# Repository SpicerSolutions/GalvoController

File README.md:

# GalvoController
Output ILDA signals using an Arduino or similar

Disclosure.

This schematic is from the following instructable

https://www.instructables.com/id/Arduino-Laser-Show-With-Real-Galvos/

And the board layout is inspired by LevTronics design of the above.

https://www.instructables.com/member/LevTronic/

I'm not an electronics engineer so I take no responsibilty for any issues with the board or design. If you have any advice or helpful amendments please let me know or submit a Pull Request.

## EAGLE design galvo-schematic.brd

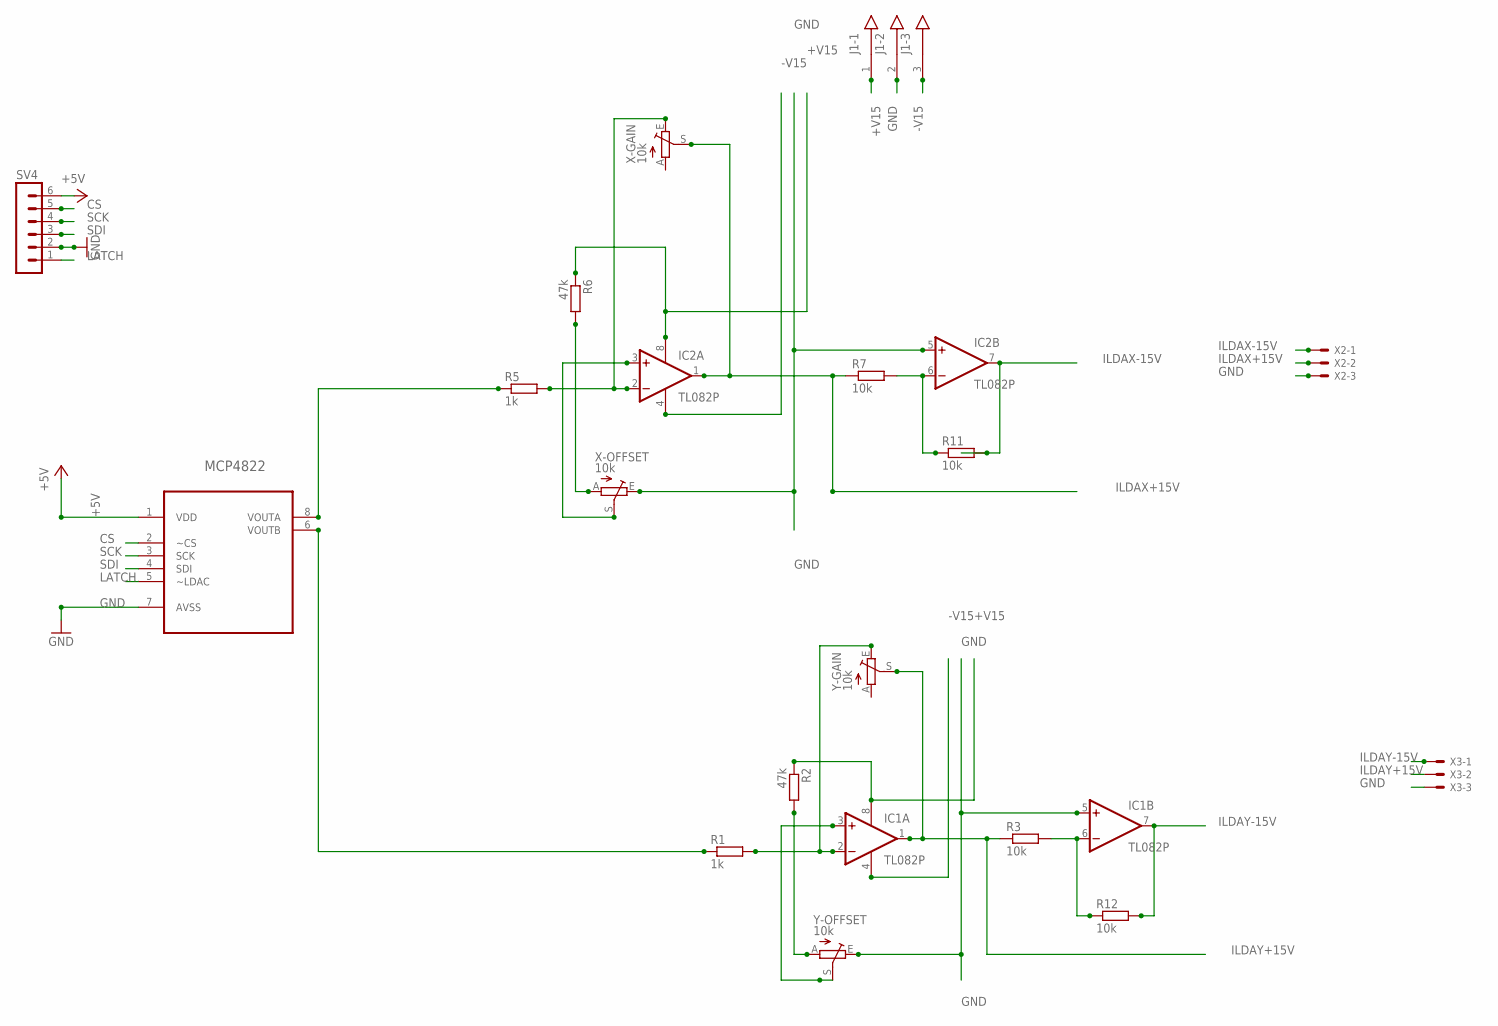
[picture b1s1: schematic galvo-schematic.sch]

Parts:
IC1, IC2: TL082P; DIL08
J1: 0022272031; KK6410-2031_3-PIN
MCP4822: MCP4822-E/P; DIP254P762X432-8
R1, R5: 1k; 0207/10
R2, R6: 47k; 0207/10
R3, R7, R11, R12: 10k; 0207/10
SV4: MA06-1
X2, X3: JST-XH-03-PIN-ROUND-PAD; JST-XH-03-PACKAGE-ROUND-PAD
X-GAIN: 10k; B25P
X-OFFSET: 10k; B25P
Y-GAIN: 10k; B25P
Y-OFFSET: 10k; B25P

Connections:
+5V: MCP4822.1 (VDD), SV4.6
+V15: IC1.8 (V+), IC2.8 (V+), J1.1, R2.1, R6.1
-V15: IC1.4 (V-), IC2.4 (V-), J1.3
CS: MCP4822.2 (~CS), SV4.5
GND: IC1.5 (+IN), IC2.5 (+IN), J1.2, MCP4822.7 (AVSS), SV4.2, X2.3, X3.3, X-OFFSET.E, Y-OFFSET.E
ILDAX+15V: IC2.1 (OUT), R7.1, X2.2, X-GAIN.S
ILDAX-15V: IC2.7 (OUT), R11.2, X2.1
ILDAY+15V: IC1.1 (OUT), R3.1, X3.2, Y-GAIN.S
ILDAY-15V: IC1.7 (OUT), R12.2, X3.1
LATCH: MCP4822.5 (~LDAC), SV4.1
unnamed: IC1.6 (-IN), R3.2, R12.1
unnamed: R2.2, Y-OFFSET.A
unnamed: IC2.6 (-IN), R7.2, R11.1
unnamed: IC1.3 (+IN), Y-OFFSET.S
unnamed: IC1.2 (-IN), R1.2, Y-GAIN.E
unnamed: MCP4822.6 (VOUTB), R1.1
unnamed: R6.2, X-OFFSET.A
unnamed: IC2.2 (-IN), R5.2, X-GAIN.E
unnamed: IC2.3 (+IN), X-OFFSET.S
unnamed: MCP4822.8 (VOUTA), R5.1
SCK: MCP4822.3 (SCK), SV4.4
SDI: MCP4822.4 (SDI), SV4.3

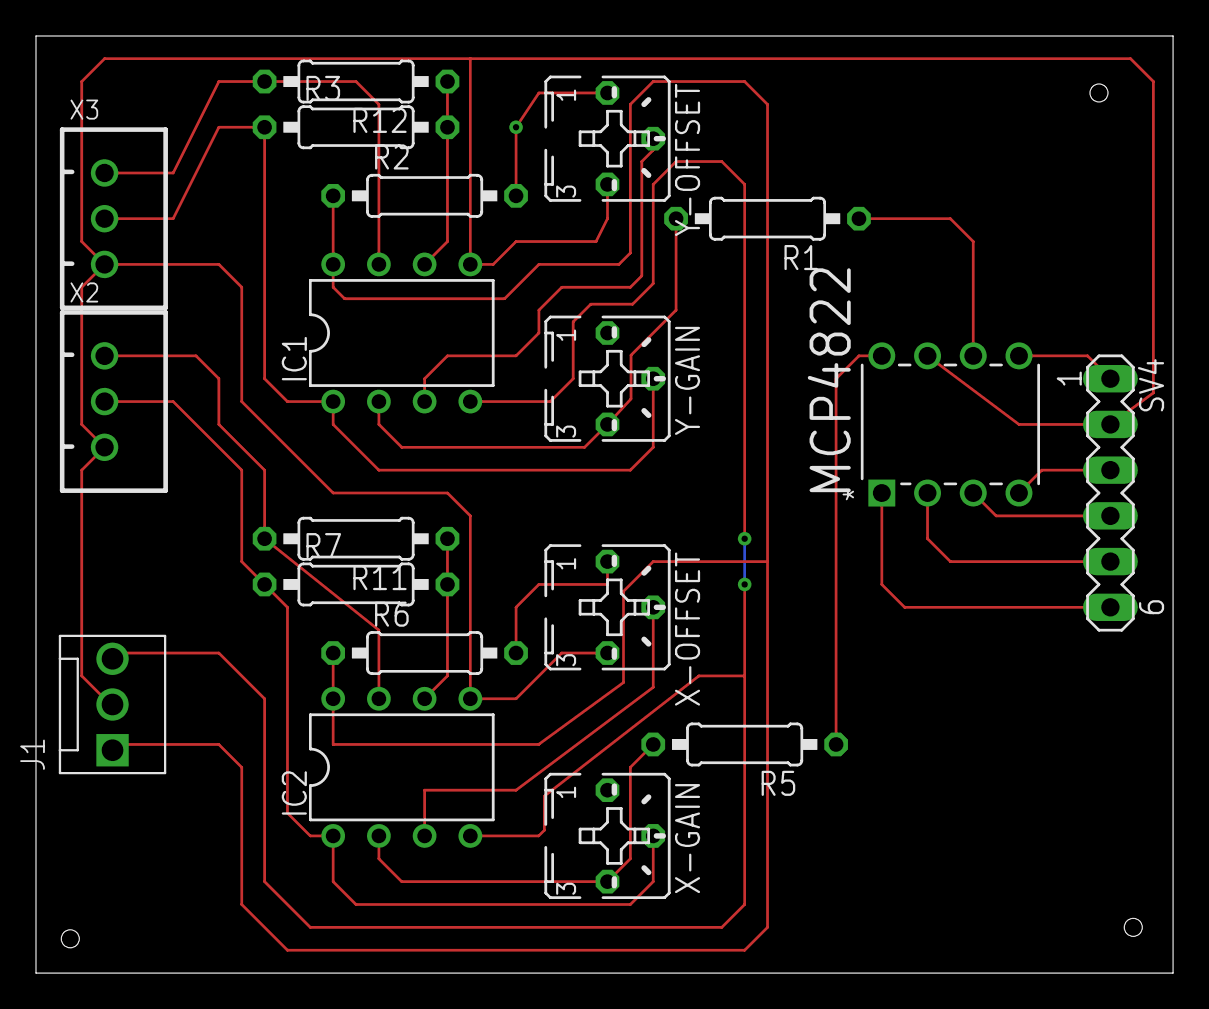
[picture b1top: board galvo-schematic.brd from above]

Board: 2 copper layers, 63.2 x 52.1 mm, 19 parts (0 on the bottom side), 22 nets.

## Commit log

2018-04-21 Eagle schematic and board files.
2018-04-21 Added disclosure
2018-04-21 Gerber files for the schematic

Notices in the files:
parts and their libraries:
volks73-Molex: Creative Commons Attribution-ShareAlike 3.0 Unported (CC BY-SA 3.0), http://creativecommons.org/licenses/by-sa/3.0/.
